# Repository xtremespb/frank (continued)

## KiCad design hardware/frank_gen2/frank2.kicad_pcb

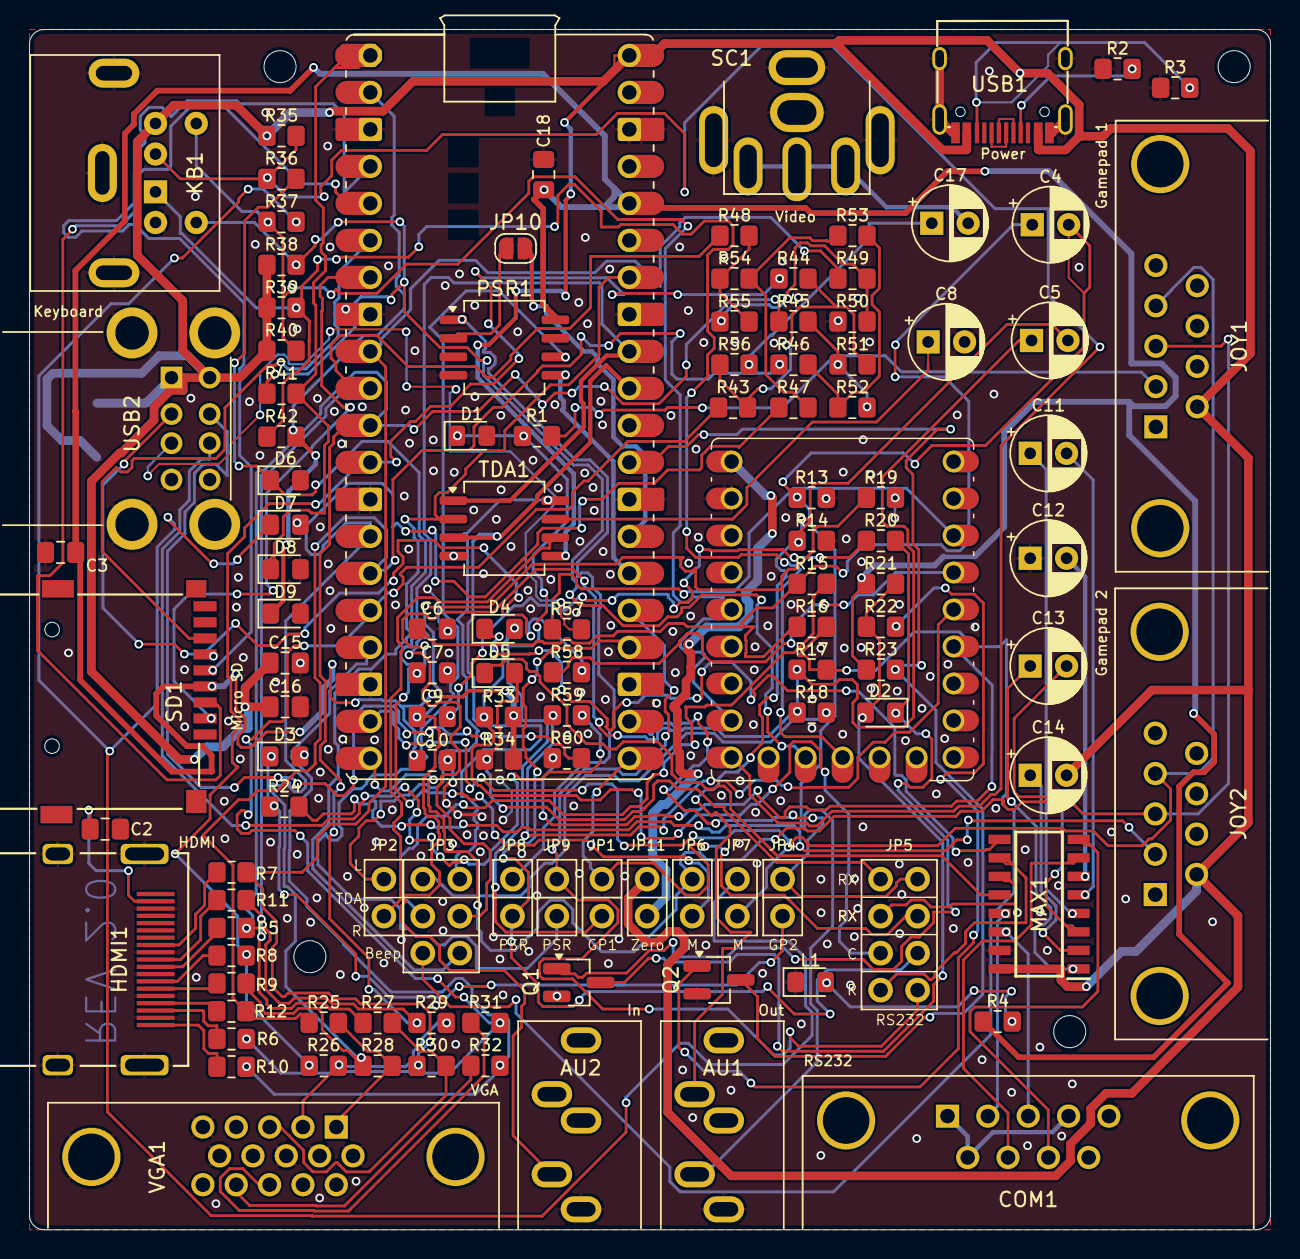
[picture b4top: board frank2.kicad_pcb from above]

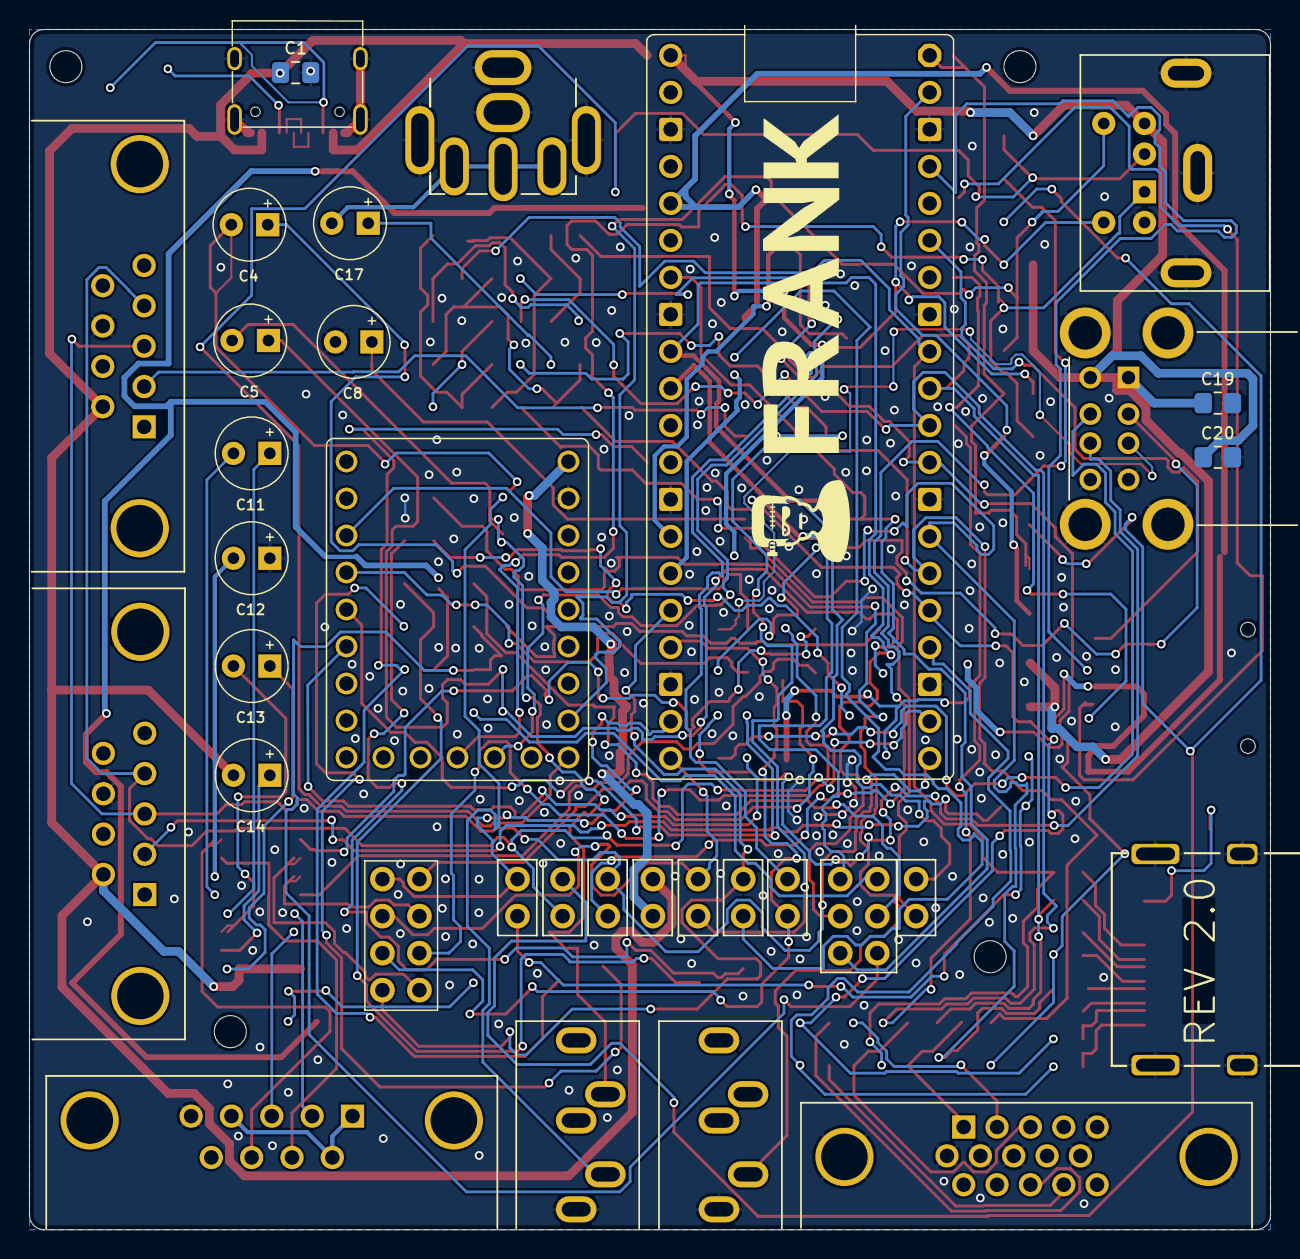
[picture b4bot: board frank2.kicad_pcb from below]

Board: 2 copper layers, 85.2 x 82.4 mm, 124 parts (3 on the bottom side), 110 nets.

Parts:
AU1: AUDIO OUT; Medved_Jack_3.5mm_CUI_SJ1-3535NG_Horizontal
AU2: AUDIO IN; Medved_Jack_3.5mm_CUI_SJ1-3535NG_Horizontal
C1: 10u; Medved_C_0805
C2, C3, C9, C10, C15, C16, C18: 0.1u; Medved_C_0805
C4, C5, C8: 10u; Medved_CP_Radial_D5.0mm_P2.50mm
C6, C7: 10n; Medved_C_0805
C11, C12, C13, C14: 1u; Medved_CP_Radial_D5.0mm_P2.50mm
C17: 220u; Medved_CP_Radial_D5.0mm_P2.50mm
C19, C20: 10u; Medved_R_0805
COM1: RS232; DB9
D1, D3, D6, D7, D8, D9: 3V3; Medved_D_0805
D2: 4148; Medved_D_0805
D4, D5: 1N4148; Medved_D_0805
H1, H2, H3, H4: MountingHole; Medved_MountingHole_V2
HDMI1: HDMI
JOY1, JOY2: Joystick; DB9
JP1, JP4, JP6, JP7, JP8, JP9, JP11: RP ZERO +5V Jumper; Medved_PinHeader_1x02_P2.54mm_Vertical_R
JP2: I2S; Medved_PinHeader_1x02
JP3: Audio Jumpers; Medved_JMP_2x03
JP5: RS232 Jumpers; Medved_PinHeader_2x04_P2.54mm_Vertical
JP10: JMP PSRAM; SolderJumper-2_P1.3mm_Open_RoundedPad1.0x1.5mm
KB1: PS/2; Connector_Mini-DIN_Female_6Pin_2rows
L1: GREEN; Medved_L_0805
MAX1: MAX232CSE+; SOIC127P600X175-16N
PSR1: PSRAM; SO-8_5.3x6.2mm_P1.27mm
Q1, Q2: BC850; SOT-23_Handsoldering
R1, R15, R18, R23, R24, R28, R29, R30, R35, R38, R39, R40: 1k; Medved_R_0805
R2, R3: 5.1K; Medved_R_0805
R4, R33, R34: 1K; Medved_R_0805
R5, R6, R7, R8, R9, R10, R11, R12, R44, R45, R46, R47, R48, R49: 270R; Medved_R_0805
R13, R14, R25, R26, R27: 330R; Medved_R_0805
R16, R17: 2k; Medved_R_0805
R19, R31, R32, R36, R37, R41, R42: 100R; Medved_R_0805
R20, R21, R22: 10k; Medved_R_0805
R43: 750R*; Medved_R_0805
R50: 300R; Medved_R_0805
R51, R52, R53, R54, R55: 150R; Medved_R_0805
R56: 51R*; Medved_R_0805
R57, R58, R59, R60: 22R; Medved_R_0805
RP1: RP2040 Pico; Raspberry_Pi_Pico_SMT_THT_MOD_2
RP2: RP 2040 Zero; rp2040-zero-tht
SC1: VIDEO (Soft Composite); AV_MOD_III-8.4-5
SD1: Micro SD; Medved_SD_Card
TDA1: TDA1387T; SO-8_5.3x6.2mm_P1.27mm
USB1: USB Type C; USB-TYPE-C-31-M-12_lib2
USB2: USB_A_Stacked; Medved_USB_A_CUI_UJ2-ADH-TH_Horizontal_Stacked
VGA1: VGA; Medved_DSUB-15-HD_Female_Horizontal

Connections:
+3V3: C3.2, C10.1, C18.1, PSR1.8 (VCC), R4.2, R21.1, R23.1, R33.2, R34.2, RP1.36 (3V3_OUT), SD1.4 (VDD)
/Audio/BEEP_OUT: JP3.5, R16.2, R17.2
/Audio/FLT: C8.1, TDA1.7 (FLT)
/Audio/L: AU1.T, C4.2, R13.1
/Audio/LEFT_OUT: JP3.3, R15.2
/Audio/LEFT_TDA: JP2.2, TDA1.6 (A_LEFT)
/Audio/LOAD_IN: AU2.T, C9.1, R19.1
/Audio/R: AU1.R, C5.2, R14.1
/Audio/RIGHT_OUT: JP3.1, R18.2
/Audio/RIGHT_TDA: JP2.1, TDA1.8 (A_RIGHT)
/Composite Video/CVBS: C17.2, SC1.1
/GPIO0: D8.1 (K), R41.2, RP1.1 (GP0)
/GPIO1: D9.1 (K), R42.2, RP1.2 (GP1)
/GPIO2: RP1.4 (GP2), SD1.5 (CLK)
/GPIO3: RP1.5 (GP3), SD1.3 (CMD)
/GPIO4: RP1.6 (GP4), SD1.7 (DAT0)
/GPIO5: RP1.7 (GP5), SD1.2 (DAT3/CD)
/GPIO6: R7.2, R30.1, R49.1, RP1.9 (GP6)
/GPIO7: R11.2, R27.1, R48.1, RP1.10 (GP7)
/GPIO8: R5.2, R29.1, R45.1, RP1.11 (GP8)
/GPIO9: R8.2, R26.1, R44.1, RP1.12 (GP9)
/GPIO10: R9.2, R28.1, R47.1, RP1.14 (GP10)
/GPIO11: R12.2, R25.1, R46.1, RP1.15 (GP11)
/GPIO12: R6.2, R31.2, R43.1, RP1.16 (GP12)
/GPIO13: R10.2, R32.2, RP1.17 (GP13)
/GPIO14: JOY1.4, JOY2.4, JP7.2 (B), RP1.19 (GP14)
/GPIO15: JOY1.3, JOY2.3, JP6.1 (A), RP1.20 (GP15)
/GPIO16: JP1.1 (A), JP5.4, RP1.21 (GP16)
/GPIO17: JP4.1 (A), JP5.2, RP1.22 (GP17)
/GPIO18: JP5.6, JP8.2 (B), RP1.24 (GP18)
/GPIO19: JP5.8, JP9.1 (A), RP1.25 (GP19)
/GPIO20: PSR1.5 (SI/SIO), RP1.26 (GP20)
/GPIO21: JP10.2 (B), RP1.27 (GP21)
/GPIO22: Q2.3 (C), R23.2, RP1.29 (GP22)
/GPIO26: JP3.2, RP1.31 (GP26_ADC0), TDA1.3 (DATA)
/GPIO27: JP3.4, RP1.32 (GP27_ADC1), TDA1.1 (SCLK)
/GPIO28: JP3.6, RP1.34 (GP28_ADC2), TDA1.2 (LRCK)
/Gamepad 1/J2_DATA: JOY1.2, R1.2
/Gamepad 2/J2_DATA: JOY2.2, R24.2
/HDMI/CLKN: HDMI1.12 (CLKN), R7.1
/HDMI/CLKP: HDMI1.10 (CLKP), R11.1
/HDMI/D0N: HDMI1.9 (D0N), R5.1
/HDMI/D0P: HDMI1.7 (D0P), R8.1
/HDMI/D1N: HDMI1.6 (D1N), R9.1
/HDMI/D1P: HDMI1.4 (D1P), R12.1
/HDMI/D2N: HDMI1.3 (D2N), R6.1
/HDMI/D2P: HDMI1.1 (D2P), R10.1
/HDMI/VBUS: C2.1, HDMI1.18 (+5V)
/Power/D+: USB1.6 (DP1), USB1.8 (DP2)
/Power/D-: USB1.5 (DN2), USB1.7 (DN1)
/RS232/C1+: C13.1, MAX1.1 (C1+)
/RS232/C1-: C13.2, MAX1.3 (C1-)
/RS232/C2+: C11.1, MAX1.4 (C2+)
/RS232/C2-: C11.2, MAX1.5 (C2-)
/RS232/CTS_IN: COM1.7, MAX1.7 (T2OUT)
/RS232/CTS_MAX: D4.1 (K), MAX1.9 (R2OUT)
/RS232/CTS_PICO: D4.2 (A), JP5.5, R33.1
/RS232/RTS_IN: COM1.8, MAX1.8 (R2IN)
/RS232/RTS_PICO: JP5.7, MAX1.10 (T2IN)
/RS232/RX_IN: COM1.3, MAX1.14 (T1OUT)
/RS232/RX_MAX: D5.1 (K), MAX1.12 (R1OUT)
/RS232/RX_PICO: D5.2 (A), JP5.1, R34.1
/RS232/TX_IN: COM1.2, MAX1.13 (R1IN)
/RS232/TX_PICO: JP5.3, MAX1.11 (T1IN)
/RS232/V+: C14.1, MAX1.2 (V+)
/RS232/V-: C12.2, MAX1.6 (V-)
/VGA/VGA_BH: R27.2, R30.2, VGA1.3
/VGA/VGA_GH: R26.2, R29.2, VGA1.2
/VGA/VGA_HS: R31.1, VGA1.13
/VGA/VGA_RH: R25.2, R28.2, VGA1.1
/VGA/VGA_VS: R32.1, VGA1.14
/ZGPIO2: R57.1, RP2.3 (2)
/ZGPIO3: R58.1, RP2.4 (3)
/ZGPIO4: R59.1, RP2.5 (4)
/ZGPIO5: R60.1, RP2.6 (5)
/ZGPIO11: KB1.1, R39.2, R42.1, RP2.12 (11)
/ZGPIO12: KB1.5, R38.2, R41.1, RP2.13 (12)
/ZGPIO14: KB1.2, R35.2, R36.1, RP2.15 (14)
/ZGPIO15: KB1.6, R37.1, R40.2, RP2.16 (15)
GND: AU1.S, AU2.S, C1.2, C2.2, C3.1, C6.2, C7.2, C8.2, C10.2, C12.1, C15.2, C16.2, C18.2, C19.2, C20.2, COM1.5, D1.2 (A), D3.2 (A), D6.2 (A), D7.2 (A), D8.2 (A), D9.2 (A), HDMI1.2 (G_D2), HDMI1.5 (G_D1), HDMI1.8 (G_D0), HDMI1.11 (G_CLK), HDMI1.17 (G_DDC/CEC), HDMI1.20 (SHIELD1), HDMI1.21 (SHIELD2), HDMI1.22 (SHIELD3), HDMI1.23 (SHIELD4), JOY1.8, JOY2.8, KB1.3, L1.1 (K), MAX1.15 (GND), PSR1.4 (VSS), Q1.2 (E), Q2.2 (E), R2.1, R3.1, R13.2, R14.2, R19.2, R50.1, RP1.3 (GND), RP1.8 (GND), RP1.13 (GND), RP1.18 (GND), RP1.23 (GND), RP1.28 (GND), RP1.33 (GND_AGND), RP1.38 (GND), RP2.22 (GND), SC1.2, SD1.6 (VSS), TDA1.4 (AGND), USB1.1 (GND), USB1.12 (GND), USB1.13 (SHIELD), USB2.4 (GND1), USB2.8 (GND2), USB2.9 (Shield), VGA1.0, VGA1.5, VGA1.6, VGA1.7, VGA1.8, VGA1.10
unnamed: C4.1, C6.1, R15.1, R16.1
unnamed: C5.1, C7.1, R17.1, R18.1
unnamed: C9.2, R20.1
unnamed: C17.1, R56.2
unnamed: COM1.1, COM1.4, COM1.6
unnamed: D1.1 (K), JP1.2 (B), R1.1
unnamed: D2.2 (A), Q1.3 (C), R21.2, R22.1
unnamed: D2.1 (K), Q1.1 (B), R20.2
unnamed: D3.1 (K), JP4.2 (B), R24.1
unnamed: D6.1 (K), JP6.2 (B), R36.2
unnamed: D7.1 (K), JP7.1 (A), R37.2
unnamed: JP8.1 (A), PSR1.1 (~CE)
unnamed: JP9.2 (B), PSR1.6 (SCLK)
unnamed: JP10.1 (A), PSR1.2 (SO/SIO)
unnamed: JP11.2 (B), RP2.23 (5V)
unnamed: L1.2 (A), R4.1
unnamed: Q2.1 (B), R22.2
unnamed: R43.2, R44.2, R51.2, R56.1
unnamed: R45.2, R51.1, R52.2
unnamed: R46.2, R52.1, R53.2
unnamed: R47.2, R53.1, R54.2
unnamed: R48.2, R54.1, R55.2
unnamed: R49.2, R50.2, R55.1
unnamed: R2.2, USB1.4 (CC1)
unnamed: R3.2, USB1.10 (CC2)
unnamed: R57.2, USB2.3 (D1+)
unnamed: R58.2, USB2.2 (D1-)
unnamed: R59.2, USB2.7 (D2+)
unnamed: R60.2, USB2.6 (D2-)
VBUS: C1.1, C14.2, C15.1, C16.1, C19.1, C20.1, JOY1.6, JOY2.6, JP11.1 (A), KB1.4, MAX1.16 (VCC), R35.1, R38.1, R39.1, R40.1, RP1.40 (VBUS), TDA1.5 (VA), USB1.2 (VBUS), USB1.11 (VBUS), USB2.1 (VBUS1), USB2.5 (VBUS2)

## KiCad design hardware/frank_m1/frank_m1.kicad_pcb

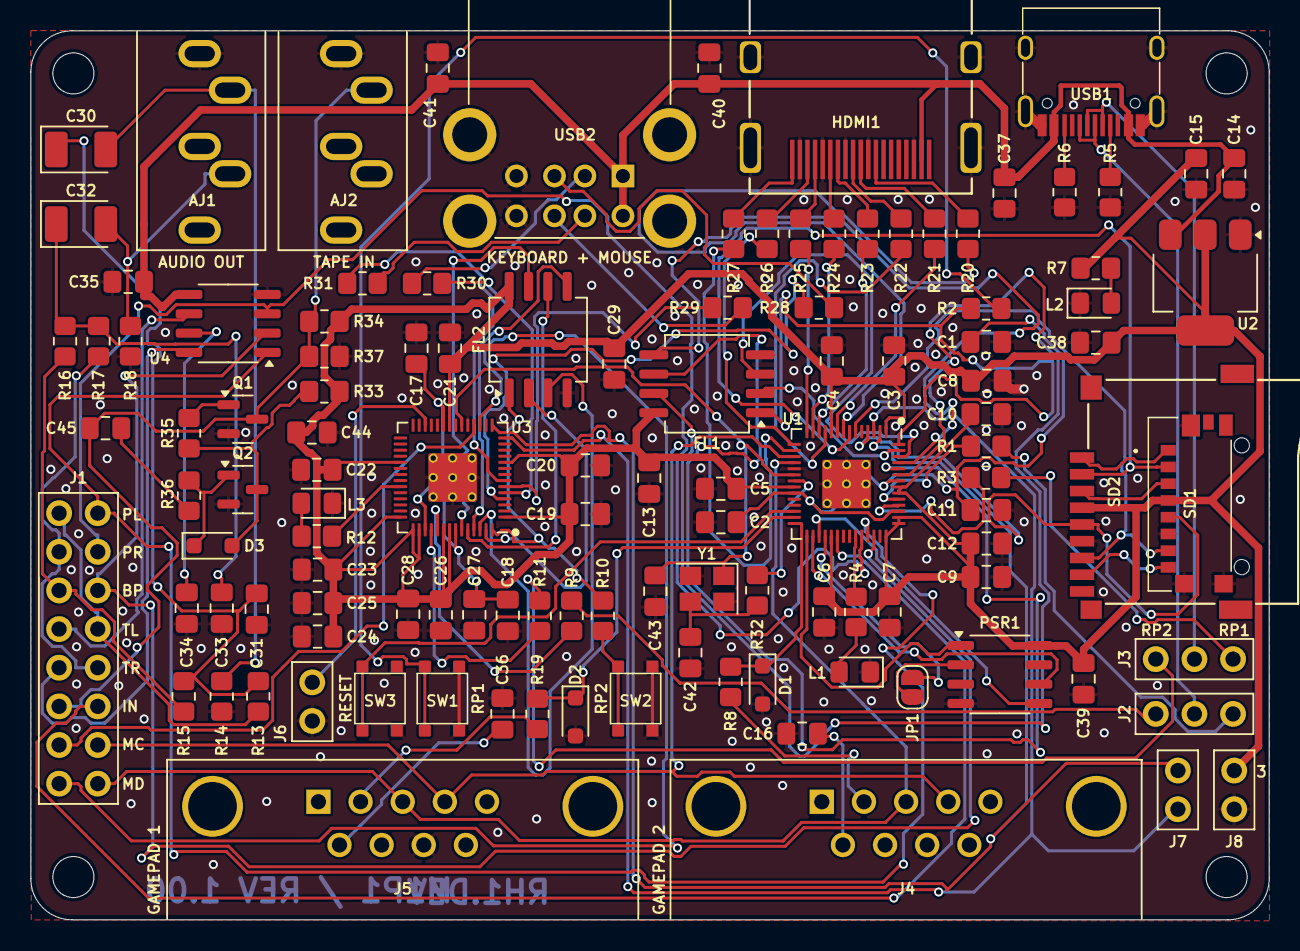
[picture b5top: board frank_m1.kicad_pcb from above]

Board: 2 copper layers, 81.4 x 58.4 mm, 121 parts (0 on the bottom side), 107 nets.

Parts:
AJ1, AJ2: SJ1-353XNG; Jack (3.5mm)
C1, C2, C3, C4, C5, C6, C7, C8, C9, C10, C13, C16, C17, C18, C19, C20, C21, C22, C23, C24, C25, C26, C29, C36, C37, C38, C39, C44, C45: 100n; Capacitor (0805)
C11, C12, C27, C28, C34: 1u; Capacitor (0805)
C14, C15, C40, C41: 10u; Capacitor (0805)
C30, C32: 10u; Capacitor (3528, tantalum, polar)
C31, C33: 10n; Capacitor (0805)
C35: 47u; Capacitor (0805)
C42, C43: 15p; Capacitor (0805)
D1, D2: 3V3; Diode (SOD-323)
D3: 1N4148; Diode (SOD-323)
FL1, FL2: W25Q128JVSIQ; SOIC-8
H1, H2, H3, H4: MountingHole; MountingHole_2.7mm
HDMI1: DC3RX19JA2; HDMI (female)
J1: Main Jumpers; Pin Header (2x08)
J2: USB DP Jumper; Pin Header (1x03)
J3: USB DM Jumper; Pin Header (1x03)
J4, J5: Gamepad; D-SUB (9 pin, male, top mount)
J6: RP2 Reset; Pin Header (1x02)
J7: UART; Pin Header (1x02)
J8: +3.3V; Pin Header (1x02)
JP1: Jumper PSRAM (2.54); Jumper (solder)
L1, L3: Blue; LED (0805)
L2: Green; LED (0805)
PSR1: ESP-PSRAM32; SO-8
Q1, Q2: BC850; SOT-23
R1, R3, R9, R11: 27R; Resistor (0805)
R2, R4, R7, R8, R10, R12, R13, R17, R19, R32, R34: 1K; Resistor (0805)
R5, R6: 5.1K; Resistor (0805)
R14, R18: 330R; Resistor (0805)
R15, R16: 2K; Resistor (0805)
R20, R21, R22, R23, R24, R25, R26, R27: 270R; Resistor (0805)
R28, R29, R30, R31: 22R; Resistor (0805)
R33, R35, R36: 10K; Resistor (0805)
R37: 100R; Resistor (0805)
SD1: 47571-0001; MicroSD (SMD, short)
SD2: 104031-0811; MicroSD (SMD, long)
SW1, SW2: KLS7-TS3302; Button (SMD, 3x3mm, 1-1)
SW3: KLS7-TS3302; Button (SMD, 3x3mm)
U1, U3: RP2040; QFN 56
U2: NCP1117 3.3; SOT-223
U4: TDA1387T; SO-8
USB1: USB4215; USB Type C
USB2: SS-52100-004; USB Type A (stacked)
Y1: 12 MHz; Crystal (3225)

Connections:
+3V3: C3.1, C4.1, C5.1, C6.1, C7.1, C8.1, C9.1, C10.1, C12.1, C13.1, C15.1, C19.1, C20.1, C21.1, C22.1, C23.1, C24.1, C25.1, C26.1, C28.1, C29.1, C38.2, C39.1, C44.1, FL1.8 (VCC), FL2.8 (VCC), J8.1, PSR1.8 (VCC), R7.2, R33.1, R34.1, SD1.P4 (VDD), SD2.4 (VDD), U1.1 (IOVDD), U1.10 (IOVDD), U1.22 (IOVDD), U1.33 (IOVDD), U1.42 (IOVDD), U1.43 (ADC_AVDD), U1.44 (VREG_IN), U1.48 (USB_VDD), U1.49 (IOVDD), U2.2 (VO), U3.1 (IOVDD), U3.10 (IOVDD), U3.22 (IOVDD), U3.33 (IOVDD), U3.42 (IOVDD), U3.43 (ADC_AVDD), U3.44 (VREG_IN), U3.48 (USB_VDD), U3.49 (IOVDD)
/A_OUTB: J1.5, R15.2, R16.2
/A_OUTL: J1.1, J1.8, R13.2
/A_OUTR: J1.3, J1.10, R17.2
/A_TDAL: J1.7, U4.6 (A_LEFT)
/A_TDAR: J1.9, U4.8 (A_RIGHT)
/Audio Out/L: AJ1.T, C30.2, R14.1
/Audio Out/R: AJ1.R, C32.2, R18.1
/GPIO0: J7.1, U1.2 (GPIO0), U3.15 (GPIO12)
/GPIO1: J7.2, U1.3 (GPIO1), U3.14 (GPIO11)
/GPIO2: SD1.P5 (CLK), SD2.5 (CLK), U1.4 (GPIO2)
/GPIO3: SD1.P3 (CMD), SD2.3 (CMD)
/GPIO4: SD1.P7 (DAT0), SD2.7 (DAT0), U1.6 (GPIO4)
/GPIO5: SD1.P2 (CD/DAT3), SD2.2 (DAT3/CD), U1.7 (GPIO5)
/GPIO6: R20.2, U1.8 (GPIO6)
/GPIO7: R21.2, U1.9 (GPIO7)
/GPIO8: R22.2, U1.11 (GPIO8)
/GPIO9: R23.2, U1.12 (GPIO9)
/GPIO10: R24.2, U1.13 (GPIO10)
/GPIO11: R25.2, U1.14 (GPIO11)
/GPIO12: R26.2, U1.15 (GPIO12)
/GPIO13: R27.2, U1.16 (GPIO13)
/GPIO14: J1.14, J4.4, J5.4, U1.17 (GPIO14)
/GPIO15: J1.16, J4.3, J5.3, U1.18 (GPIO15)
/GPIO16: D2.1 (K), R19.1, U1.27 (GPIO16)
/GPIO17: D1.1 (K), R8.1, U1.28 (GPIO17)
/GPIO18: PSR1.1 (~CE), U1.29 (GPIO18)
/GPIO19: PSR1.6 (SCLK), U1.30 (GPIO19)
/GPIO20: PSR1.5 (SI/SIO), U1.31 (GPIO20)
/GPIO21: JP1.2 (B), U1.32 (GPIO21)
/GPIO22: J1.12, U1.34 (GPIO22)
/GPIO26: J1.4, U1.38 (GPIO26_ADC0), U4.3 (DATA)
/GPIO27: J1.2, U1.39 (GPIO27_ADC1), U4.1 (SCLK)
/GPIO28: J1.6, U1.40 (GPIO28_ADC2), U4.2 (LRCK)
/Gamepad 1/+5V: C36.1, J5.6
/Gamepad 1/J1_DATA: J5.2, R19.2
/Gamepad 2/+5V: C16.1, J4.6
/Gamepad 2/J1_DATA: J4.2, R8.2
/LOAD_IN: AJ2.T, C45.1, J1.11, Q1.3 (C), R34.2, R37.1
/MS_CLK: J1.13, U3.18 (GPIO15)
/MS_DATA: J1.15, U3.17 (GPIO14)
/Micro SD/DAT1: SD1.P8 (DAT1), SD2.8 (DAT1)
/Micro SD/DAT2: SD1.P1 (DAT2), SD2.1 (DAT2)
/P_DM: J3.2, USB1.5 (DN2), USB1.7 (DN1)
/P_DP: J2.2, USB1.6 (DP1), USB1.8 (DP2)
/RP1/GPIO25: R4.2, U1.37 (GPIO25)
/RP1/QSPI_SCLK: FL1.6 (CLK), U1.52 (QSPI_SCLK)
/RP1/QSPI_SD0: FL1.5 (DI(IO0)), U1.53 (QSPI_SD0)
/RP1/QSPI_SD1: FL1.2 (DO(IO1)), U1.55 (QSPI_SD1)
/RP1/QSPI_SD2: FL1.3 (IO2), U1.54 (QSPI_SD2)
/RP1/QSPI_SD3: FL1.7 (IO3), U1.51 (QSPI_SD3)
/RP1/QSPI_SS: FL1.1 (~CS), R2.1, U1.56 (QSPI_SS)
/RP1/~USB_BOOT: R2.2, SW1.2
/RP1_DM: J3.1, R3.1
/RP1_DP: J2.1, R1.1
/RP2/GPIO25: R12.2, U3.37 (GPIO25)
/RP2/QSPI_SCLK: FL2.6 (CLK), U3.52 (QSPI_SCLK)
/RP2/QSPI_SD0: FL2.5 (DI(IO0)), U3.53 (QSPI_SD0)
/RP2/QSPI_SD1: FL2.2 (DO(IO1)), U3.55 (QSPI_SD1)
/RP2/QSPI_SD2: FL2.3 (IO2), U3.54 (QSPI_SD2)
/RP2/QSPI_SD3: FL2.7 (IO3), U3.51 (QSPI_SD3)
/RP2/QSPI_SS: FL2.1 (~CS), R10.1, U3.56 (QSPI_SS)
/RP2/~USB_BOOT: R10.2, SW2.2
/RP2_DM: J3.3, R11.1
/RP2_DP: J2.3, R9.1
/RP2_RUN: J6.1, U3.26 (RUN)
/RUN: SW3.3, SW3.4, U1.26 (RUN)
/US_D1M: R30.1, U3.5 (GPIO3)
/US_D1P: R28.1, U3.4 (GPIO2)
/US_D2M: R31.1, U3.7 (GPIO5)
/US_D2P: R29.1, U3.6 (GPIO4)
/XIN: C43.1, U1.20 (XIN), U3.20 (XIN), Y1.1
/XOUT: R32.1, U1.21 (XOUT)
GND: AJ1.S, AJ2.S, C1.2, C2.2, C3.2, C4.2, C5.2, C6.2, C7.2, C8.2, C9.2, C10.2, C11.2, C12.2, C13.2, C14.2, C15.2, C16.2, C17.2, C18.2, C19.2, C20.2, C21.2, C22.2, C23.2, C24.2, C25.2, C26.2, C27.2, C28.2, C29.2, C31.2, C33.2, C34.2, C35.1, C36.2, C37.2, C38.1, C39.2, C40.2, C41.2, C42.2, C43.2, C44.2, D1.2 (A), D2.2 (A), FL1.4 (GND), FL2.4 (GND), HDMI1.2 (G_D2), HDMI1.5 (G_D1), HDMI1.8 (G_D0), HDMI1.11 (G_CLK), HDMI1.17 (G_DDC/CEC), HDMI1.20 (SHIELD1), HDMI1.21 (SHIELD2), HDMI1.22 (SHIELD3), HDMI1.23 (SHIELD4), J4.8, J5.8, J6.2, J8.2, L1.1 (K), L2.1 (K), L3.1 (K), PSR1.4 (VSS), Q1.2 (E), Q2.2 (E), R5.1, R6.1, R14.2, R18.2, R37.2, SD1.G1 (GND_1), SD1.G2 (GND_2), SD1.G3 (GND_3), SD1.P6 (VSS), SD2.6 (VSS), SW1.1, SW2.1, SW3.1, SW3.2, U1.19 (TESTEN), U1.57 (GND), U2.1 (GND), U3.19 (TESTEN), U3.57 (GND), U4.4 (AGND), USB1.1 (GND), USB1.12 (GND), USB1.13 (SHIELD), USB2.4 (GND1), USB2.8 (GND2), USB2.9 (Shield), Y1.2, Y1.4
unnamed: C30.1, C31.1, R13.1, R15.1
unnamed: C32.1, C33.1, R16.1, R17.1
unnamed: C42.1, R32.2, Y1.3
unnamed: C45.2, R36.1
unnamed: D3.2 (A), Q2.3 (C), R33.2, R35.1
unnamed: D3.1 (K), Q2.1 (B), R36.2
unnamed: HDMI1.12 (CLKN), R20.1
unnamed: HDMI1.10 (CLKP), R21.1
unnamed: HDMI1.9 (D0N), R22.1
unnamed: HDMI1.7 (D0P), R23.1
unnamed: HDMI1.6 (D1N), R24.1
unnamed: HDMI1.4 (D1P), R25.1
unnamed: HDMI1.3 (D2N), R26.1
unnamed: HDMI1.1 (D2P), R27.1
unnamed: JP1.1 (A), PSR1.2 (SO/SIO)
unnamed: L1.2 (A), R4.1
unnamed: L2.2 (A), R7.1
unnamed: L3.2 (A), R12.1
unnamed: Q1.1 (B), R35.2
unnamed: R3.2, U1.46 (USB_DM)
unnamed: R1.2, U1.47 (USB_DP)
unnamed: C1.1, C2.1, C11.1, U1.23 (DVDD), U1.45 (VREG_VOUT), U1.50 (DVDD)
unnamed: R11.2, U3.46 (USB_DM)
unnamed: R9.2, U3.47 (USB_DP)
unnamed: C17.1, C18.1, C27.1, U3.23 (DVDD), U3.45 (VREG_VOUT), U3.50 (DVDD)
unnamed: C34.1, U4.7 (FLT)
unnamed: R5.2, USB1.4 (CC1)
unnamed: R6.2, USB1.10 (CC2)
unnamed: R28.2, USB2.3 (D1+)
unnamed: R30.2, USB2.2 (D1-)
unnamed: R29.2, USB2.7 (D2+)
unnamed: R31.2, USB2.6 (D2-)
VBUS: C14.1, C35.2, C37.1, C40.1, C41.1, HDMI1.18 (+5V), U2.3 (VI), U4.5 (VA), USB1.2 (VBUS), USB1.11 (VBUS), USB2.1 (VBUS1), USB2.5 (VBUS2)

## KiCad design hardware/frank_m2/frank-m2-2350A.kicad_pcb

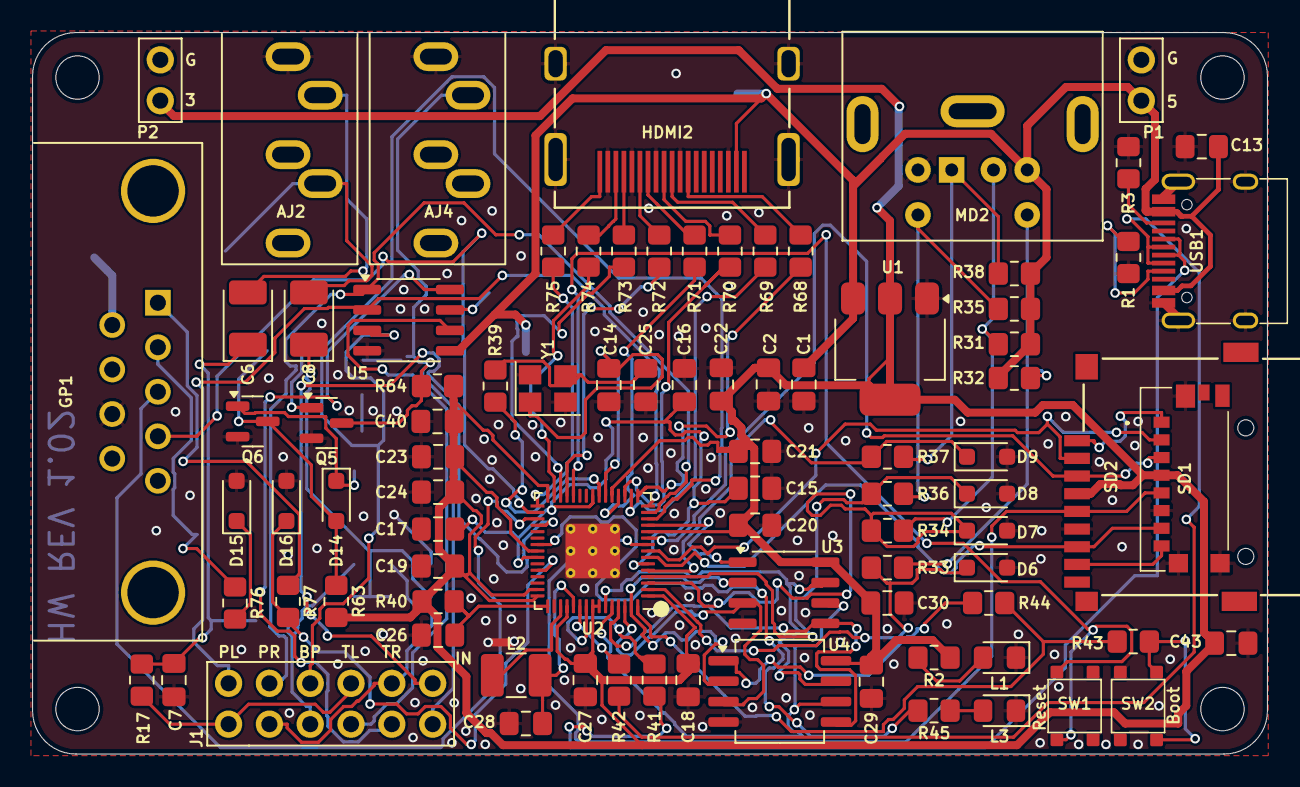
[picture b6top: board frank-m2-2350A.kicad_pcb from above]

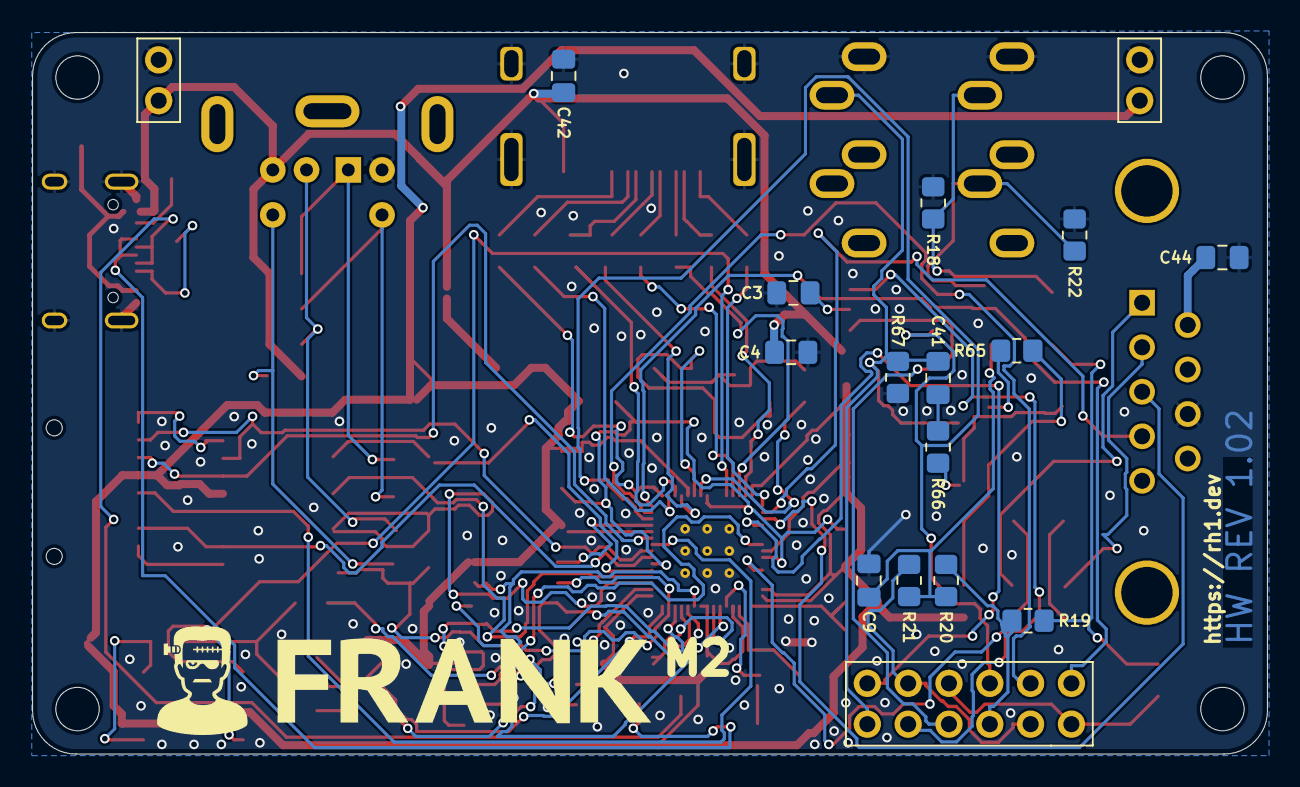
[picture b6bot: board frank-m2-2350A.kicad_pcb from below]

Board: 2 copper layers, 76.8 x 44.9 mm, 105 parts (14 on the bottom side), 85 nets.

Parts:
AJ2: SJ1-353XNG; Jack (3.5mm)
AJ4: PJ-325C; Jack (3.5mm)
C1, C2, C13: 10u; Capacitor (0805)
C3: 1u; Capacitor (0805)
C4: 47u; Capacitor (0805)
C6, C8: 10u; Capacitor (3528, tantalum, polar)
C7, C9: 10n; Capacitor (0805)
C14, C25: 15p; Capacitor (0805)
C15, C17, C18, C19, C20, C21, C22, C23, C24, C29, C30, C40, C41, C42, C43, C44: 100n; Capacitor (0805)
C16, C26, C27, C28: 4.7u; Capacitor (0805)
D6, D7, D8, D9, D15, D16: 3V3; Diode (SOD-323)
D14: 1N4148; Diode (SOD-323)
GP1: Gamepad; D-SUB (9 pin, male, top mount)
H1, H2, H3, H4: MountingHole; Mounting Hole (2.7mm)
HDMI2: HDMI Female; HDMI (female)
J1: Pin Header 2x18; Pin Header (2x06)
L1: Green; LED (0805)
L2: 3.3uH; Inductor (3225)
L3: Blue; LED (0805)
MD2: Mini-DIN-6; MiniDIN (6 Pin, female)
P1: Power (+5V); Pin Header (1x02)
P2: Power (+3.3V); Pin Header (1x02)
Q5, Q6: BC850; SOT-23
R1, R3: 5.1K; Resistor (0805)
R2, R17, R21, R31, R32, R35, R39, R43, R45, R64, R76, R77: 1K; Resistor (0805)
R18, R22: 330R; Resistor (0805)
R19, R20: 2K; Resistor (0805)
R33, R34, R36, R37, R67: 100R; Resistor (0805)
R38: 1k; Resistor (0805)
R40: 33R; Resistor (0805)
R41, R42: 27R; Resistor (0805)
R44: 0R; Resistor (0805)
R63, R65, R66: 10K; Resistor (0805)
R68, R69, R70, R71, R72, R73, R74, R75: 270R; Resistor (0805)
SD1: 47571-0001; MicroSD (SMD, short)
SD2: 104031-0811; MicroSD (SMD, long)
SW1: Reset; Button (SMD, 3x3mm, 1-1)
SW2: Boot; Button (SMD, 3x3mm, 1-1)
U1: NCP1117 3.3; SOT-223
U2: RP2350A; QFN 60 (RP2350A)
U3: ESP-PSRAM32; SO-8
U4: W25Q128JVSQ; SOIC-8
U5: TDA1387T; SO-8
USB1: USB4215-03-A; USB Type C
Y1: ABM8-272-T3 12 MHz; Crystal (3225)

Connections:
+3V3: C2.1, C18.1, C19.1, C20.1, C21.1, C22.1, C23.1, C24.1, C27.1, C29.1, C30.1, C40.1, C43.2, P2.2, R2.2, R40.1, R63.1, R64.1, SD1.P4 (VDD), SD2.4 (VDD), U1.2 (VO), U2.1 (IOVDD), U2.11 (IOVDD), U2.20 (IOVDD), U2.30 (IOVDD), U2.38 (IOVDD), U2.44 (ADC_AVDD), U2.45 (IOVDD), U2.49 (VREG_VIN), U2.53 (USB_OTP_VDD), U2.54 (QSPI_IOVDD), U3.8 (VCC), U4.8 (VCC)
/A_OUTB: J1.5, R19.2, R20.2
/A_OUTL: J1.1, J1.8, R17.2
/A_OUTR: J1.3, J1.10, R21.2
/A_TDAL: J1.7, U5.6 (A_LEFT)
/A_TDAR: J1.9, U5.8 (A_RIGHT)
/Audio Out/L: AJ2.T, C6.2, R18.1
/Audio Out/R: AJ2.R, C8.2, R22.1
/D+: R41.1, USB1.6 (DP1), USB1.8 (DP2)
/D-: R42.1, USB1.5 (DN2), USB1.7 (DN1)
/GPIO0: D6.1 (K), R33.2, U2.2 (GPIO0)
/GPIO1: D7.1 (K), R34.2, U2.3 (GPIO1)
/GPIO2: D8.1 (K), R36.2, U2.4 (GPIO2)
/GPIO3: D9.1 (K), R37.2, U2.5 (GPIO3)
/GPIO4: SD1.P7 (DAT0), SD2.7 (DAT0), U2.7 (GPIO4)
/GPIO5: SD1.P2 (CD/DAT3), SD2.2 (DAT3/CD), U2.8 (GPIO5)
/GPIO6: SD1.P5 (CLK), SD2.5 (CLK), U2.9 (GPIO6)
/GPIO7: SD1.P3 (CMD), SD2.3 (CMD), U2.10 (GPIO7)
/GPIO8: U2.12 (GPIO8), U3.1 (~CE)
/GPIO9: J1.6, U2.13 (GPIO9), U5.3 (DATA)
/GPIO10: J1.4, U2.14 (GPIO10), U5.1 (SCLK)
/GPIO11: J1.2, U2.15 (GPIO11), U5.2 (LRCK)
/GPIO12: R68.2, U2.16 (GPIO12)
/GPIO13: R69.2, U2.17 (GPIO13)
/GPIO14: R70.2, U2.18 (GPIO14)
/GPIO15: R71.2, U2.19 (GPIO15)
/GPIO16: R72.2, U2.27 (GPIO16)
/GPIO17: R73.2, U2.28 (GPIO17)
/GPIO18: R74.2, U2.29 (GPIO18)
/GPIO19: R75.2, U2.31 (GPIO19)
/GPIO20: GP1.4, U2.32 (GPIO20)
/GPIO21: GP1.3, U2.33 (GPIO21)
/GPIO22: J1.12, U2.34 (GPIO22)
/GPIO26: D15.1 (K), R76.1
/GPIO27: D16.1 (K), R77.1, U2.41 (GPIO27_ADC1)
/Gamepad/+5V: C44.1, GP1.6
/Gamepad/J1_DATA: GP1.2, R76.2
/Gamepad/J2_DATA: GP1.1, R77.2
/LOAD_IN_D: AJ4.T, C41.1, J1.11, Q5.3 (C), R64.2, R67.1
/PS2/PS/2 CLK: MD2.5, R35.2, R36.1
/PS2/PS/2 DATA: MD2.1, R37.1, R38.2
/RP2350A/FLASH_SS: R44.2, U4.1 (~CS)
/RP2350A/QSPI_SCLK: U2.56 (QSPI_SCLK), U3.6 (SCLK), U4.6 (CLK)
/RP2350A/QSPI_SD0: U2.57 (QSPI_SD0), U3.5 (SI/SIO), U4.5 (DI(IO0))
/RP2350A/QSPI_SD1: U2.59 (QSPI_SD1), U3.2 (SO/SIO), U4.2 (DO(IO1))
/RP2350A/QSPI_SD2: U2.58 (QSPI_SD2), U3.3 (SIO2), U4.3 (IO2)
/RP2350A/QSPI_SD3: U2.55 (QSPI_SD3), U3.7 (SIO3), U4.7 (IO3)
/RP2350A/QSPI_SS: R43.1, R44.1, U2.60 (QSPI_SS)
/RP2350A/VREG_AVDD: C26.1, R40.2, U2.46 (VREG_AVDD)
/RP2350A/VREG_LX: L2.2, U2.48 (VREG_LX)
/RP2350A/XIN: C14.1, U2.21 (XIN), Y1.1
/RP2350A/XOUT: R39.1, U2.22 (XOUT)
/RP2350A/~USB_BOOT: R43.2, SW2.2
/RUN: SW1.1, U2.26 (RUN)
/SD Card/DAT1: SD1.P8 (DAT1), SD2.8 (DAT1)
/SD Card/DAT2: SD1.P1 (DAT2), SD2.1 (DAT2)
GND: AJ2.S, AJ4.S, C1.2, C2.2, C3.2, C4.1, C7.2, C9.2, C13.2, C14.2, C15.2, C16.2, C17.2, C18.2, C19.2, C20.2, C21.2, C22.2, C23.2, C24.2, C25.2, C26.2, C27.2, C28.2, C29.2, C30.2, C40.2, C42.2, C43.1, C44.2, D6.2 (A), D7.2 (A), D8.2 (A), D9.2 (A), D15.2 (A), D16.2 (A), GP1.8, HDMI2.2 (G_D2), HDMI2.5 (G_D1), HDMI2.8 (G_D0), HDMI2.11 (G_CLK), HDMI2.17 (G_DDC/CEC), HDMI2.20 (SHIELD1), HDMI2.21 (SHIELD2), HDMI2.22 (SHIELD3), HDMI2.23 (SHIELD4), L1.1 (K), L3.1 (K), MD2.3, P1.1, P2.1, Q5.2 (E), Q6.2 (E), R1.1, R3.1, R18.2, R22.2, R67.2, SD1.G1 (GND_1), SD1.G2 (GND_2), SD1.G3 (GND_3), SD1.P6 (VSS), SD2.6 (VSS), SW1.2, SW2.1, U1.1 (GND), U2.47 (VREG_PGND), U2.61 (GND), U3.4 (VSS), U4.4 (GND), U5.4 (AGND), USB1.1 (GND), USB1.12 (GND), USB1.13 (SHIELD), Y1.2, Y1.4
GPIO25: R45.2, U2.37 (GPIO25)
unnamed: C6.1, C7.1, R17.1, R19.1
unnamed: C8.1, C9.1, R20.1, R21.1
unnamed: C15.1, C16.1, C17.1, U2.6 (DVDD), U2.23 (DVDD), U2.39 (DVDD)
unnamed: C25.1, R39.2, Y1.3
unnamed: C41.2, R66.1
unnamed: D14.2 (A), Q6.3 (C), R63.2, R65.1
unnamed: D14.1 (K), Q6.1 (B), R66.2
unnamed: HDMI2.12 (CLKN), R68.1
unnamed: HDMI2.10 (CLKP), R69.1
unnamed: HDMI2.9 (D0N), R70.1
unnamed: HDMI2.7 (D0P), R71.1
unnamed: HDMI2.6 (D1N), R72.1
unnamed: HDMI2.4 (D1P), R73.1
unnamed: HDMI2.3 (D2N), R74.1
unnamed: HDMI2.1 (D2P), R75.1
unnamed: L1.2 (A), R2.1
unnamed: L3.2 (A), R45.1
unnamed: MD2.2, R31.2, R34.1
unnamed: MD2.6, R32.2, R33.1
unnamed: Q5.1 (B), R65.2
unnamed: R42.2, U2.51 (USB_DM)
unnamed: R41.2, U2.52 (USB_DP)
unnamed: C28.1, L2.1, U2.50 (VREG_FB)
unnamed: C3.1, U5.7 (FLT)
unnamed: R1.2, USB1.4 (CC1)
unnamed: R3.2, USB1.10 (CC2)
VBUS: C1.1, C4.2, C13.1, C42.1, HDMI2.18 (+5V), MD2.4, P1.2, R31.1, R32.1, R35.1, R38.1, U1.3 (VI), U5.5 (VA), USB1.2 (VBUS), USB1.11 (VBUS)
